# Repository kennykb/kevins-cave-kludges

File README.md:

# kevins-cave-kludges
Supporting materials for Kludges from Kevin's Cave.

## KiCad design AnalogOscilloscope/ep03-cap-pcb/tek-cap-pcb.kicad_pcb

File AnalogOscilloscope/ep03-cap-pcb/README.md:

# Restoring a 50-Year-Old Analog Oscillope
## Episode 3: Replacing a Capacitor

This folder contains the files that were used to design the adapter to mount
a modern capacitor in place of a failed one.

Video link: [https://youtu.be/u-VB3HTjkvM]

| File | Description |
| ---- | ----------- |
| gerbers/ | Gerber files and Excellon drill files for the adapter board |
| tek-cap-pcb.kicad_pro | KiCAD project file for the adapter board |
| tek-cap-pcb.kicad_prl | KiCAD extended settings for the adapter board |
| tek-cap-pcb.kicad_sch | KiCAD schematic for the adapter board |
| tek-cap-pcb.kicad_pcb | KiCAD PCB layout for the adapter board |
| tek-cap-pcb.png | KiCAD rendering of the adapter board |

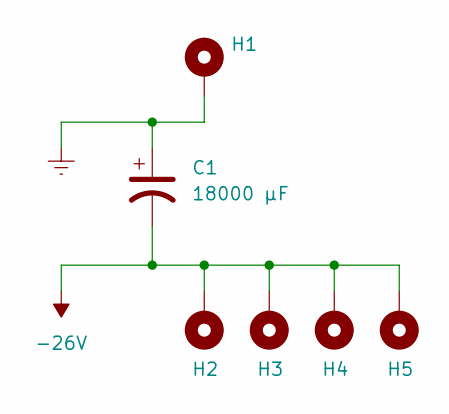
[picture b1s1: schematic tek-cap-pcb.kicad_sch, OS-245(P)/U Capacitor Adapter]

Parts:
C1: 18000 µF; CP_Radial_D35.0mm_P10.00mm_SnapIn; Manufacturer_Part# SLPX183M050H9P3
H1, H2, H3, H4, H5: MountingHole_Pad; MountingHole_2.5mm_Pad

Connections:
-26V: C1.2, H2.1, H3.1, H4.1, H5.1
Earth: C1.1, H1.1

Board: 2 copper layers, 6 parts (0 on the bottom side), 2 nets, no tracks yet.

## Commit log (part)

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2024-04-03 Episode 1: quick and dirty noise generator
2024-04-03 Add KiCAD version of schematic
2024-04-03 Move kicad/ directory to the correct place: oops!
2024-04-03 Try to correct Markdown format
2024-04-03 Typo in README.md
2024-04-04 Update README.md
    Add the YouTube link for when the video drops.
2024-04-05 Add files for Ep002: The Schmitt Trigger
2024-04-05 Update README with video location
2024-04-05 Add episode 3 files
2024-04-05 Link to Ep3 video
2024-04-06 Ep4 - add video link
2024-04-06 Markdown format blunder
2024-04-07 New episode 5 : LM311 Schmitt trigger oscillator
2024-04-07 Oops - README misnamed
2024-04-07 Multiple typos in README
2024-04-22 Files for episode 6 - oscillator with a diode bridge
2024-04-22 Ep6 YT link
2024-05-05 Transistors 101 episode 2: Current Sources - schematics
2024-05-15 Trransistors 101 episode 3: common emitterr amp 1
2024-05-15 Oops - add OSHW logo to schematics
2024-05-27 Transistors 101 ep4: Followers and Switches
2024-06-29 Transistors 101 episode 6: Biasing and Bootstrapping
2024-07-08 Audio synth ep7: the integrator
2024-07-08 YouTube upload aborted - correct link to new video
2024-07-16 Transistor 101 Episode 7: Common Emitter Amp Biasing
2024-07-16 Oops - REAMDE misnamed
2024-07-26 Transistors 101 ep8: The Quest For Current Gain
2024-08-02 Transistors 101 Episode 9: The Quest for Voltage Gain
2024-08-02 Type in Ep009 README
2024-08-02 Add OSHW logo to schematics
2024-09-12 First tranche of files for I-V curve tracer
2024-09-12 Add part 1 video link
2024-09-12 Add Python script for Schmitt trigger values in reset circuit
2024-09-12 I-V tracer files for part 3
2024-10-11 Integrator vs Low-Pass Filter
2024-10-22 Updates to I-V tracer; add episode on TL431
2024-10-22 Add YouTube link
2024-11-09 Transistors 101 episode 12: They Do It with Mirrors
2024-11-13 Update video link; reuploaded
2024-11-27 Add script that analyzed scope data, at a viewer's request
2024-11-28 Transistors 101 episode 13 links
2024-11-28 Add sample data at viewer request
2024-11-30 Change video link to reflect re-upload of the video.
2024-12-11 supporting files, audio synthesis episodes 8/9
2024-12-11 Add CircuitJS model
2024-12-11 Update README for synthesizer episode 8/9
2024-12-11 Another update to synth episode 8/9 README
2024-12-11 Update README with the video link
2024-12-18 Update video link
2025-01-10 Op-Amp Basics, episode 2
2025-01-28 Transistors 101, episode 14
2025-01-29 Transistors 101 episode 15
2025-01-29 Transistors 101 episode 15 - add video description
2025-01-30 Typos in notes on schematic
2025-02-08 Correct typo in t101ep7 page title:
2025-02-09 Transistor 101 - episodes 16-18
2025-02-25 Op-Amp Basics, episode 3
2025-03-21 op-amp basics, episode 4
2025-03-22 op-amp basics episode 4 - correct error in schematic where the ring connector of J1 is left floating while the tip connects to both channels of the output. Thanks to YouTube user @shean4 for catching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
2025-03-22 Revise common-emitter spreadsheet to make saturationv voltage an explicit output
2025-04-15 Op-amp basics, episode 5
2025-04-19 Re-uploaded op-amp basics ep5
2025-04-20 Put the opamps with (-) on top.
2025-05-06 Episode 6: Active clamps and peak detectors
2025-05-06 Add video link
2025-05-23 Add second video link
2025-05-30 Episode 7 - reducing leakage current
2025-06-13 Analog o'scope episode 3 - capacitor adapter board
2025-06-13 Fix Markdown syntax
2025-06-13 Add auto-created backup files to .gitignore
2025-07-11 Op-amp basics, ep9
2025-08-01 Audio synthesis ep10
2025-09-05 Analog audio synthesis ep12
2025-09-06 Revise Audio Synthesis ep12 video link to version *without* burnt-in captions
2025-10-17 Op-amp basics, ep11 - the differentiator
2025-12-19 AC Amp, op-amp basics #12, first tranche
2025-12-19 AC Amp, op-amp basics #12, second tranche
2025-12-19 AC Amp, op-amp basics #12, file list with video link
2025-12-19 Add script that produced the Bode plots, at the request of viewer @NNNILabs
2026-01-25 Op-Amp Basics, episode 13: transimpedance amplifier
2026-01-25 Make directory name systematic
2026-02-20 Missing videl link!
2026-02-20 Op-amp basics, ep14
2026-02-28 Op-amp Basics ep15
2026-03-12 Op-amp basics ep16: Howland current pump
2026-05-01 Op-amp basics, ep17
2026-05-13 Correct pinout of DMMT5401
2026-06-05 Transistors 101 episode 19 - BJT power amps part 1
2026-06-05 Wrong file extension on README.md
2026-06-05 Correct README.md formatting errors
2026-06-10 Get rid of pre-released (and incorrect) drafts of later episodes
